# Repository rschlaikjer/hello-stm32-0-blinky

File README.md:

# STM32 Programming with opencm3: Part 0

This repository contains the complete companion code and EAGLE design files
to accompany
[this blog post](https://rhye.org/post/stm32-with-opencm3-0-compiling-and-uploading/),
which details the basics of compiling and flashing code to a `STM32F0`-series MCU.

In this repo:
- `main.cpp`: The main application code. Contains a simple example using GPIOs
and the SysTick timer.
- `stm32f0.ld`: Linker script for the `STM32F070CB` MCU
- `Makefile`: Collection of rules to build and upload code to the MCU
- `.gdbinit`: GDB resource file that automates conencting to an attached Black Magic Probe
- `libopencm3`: Git submodule referencing our version of opencm3.

## Pictures

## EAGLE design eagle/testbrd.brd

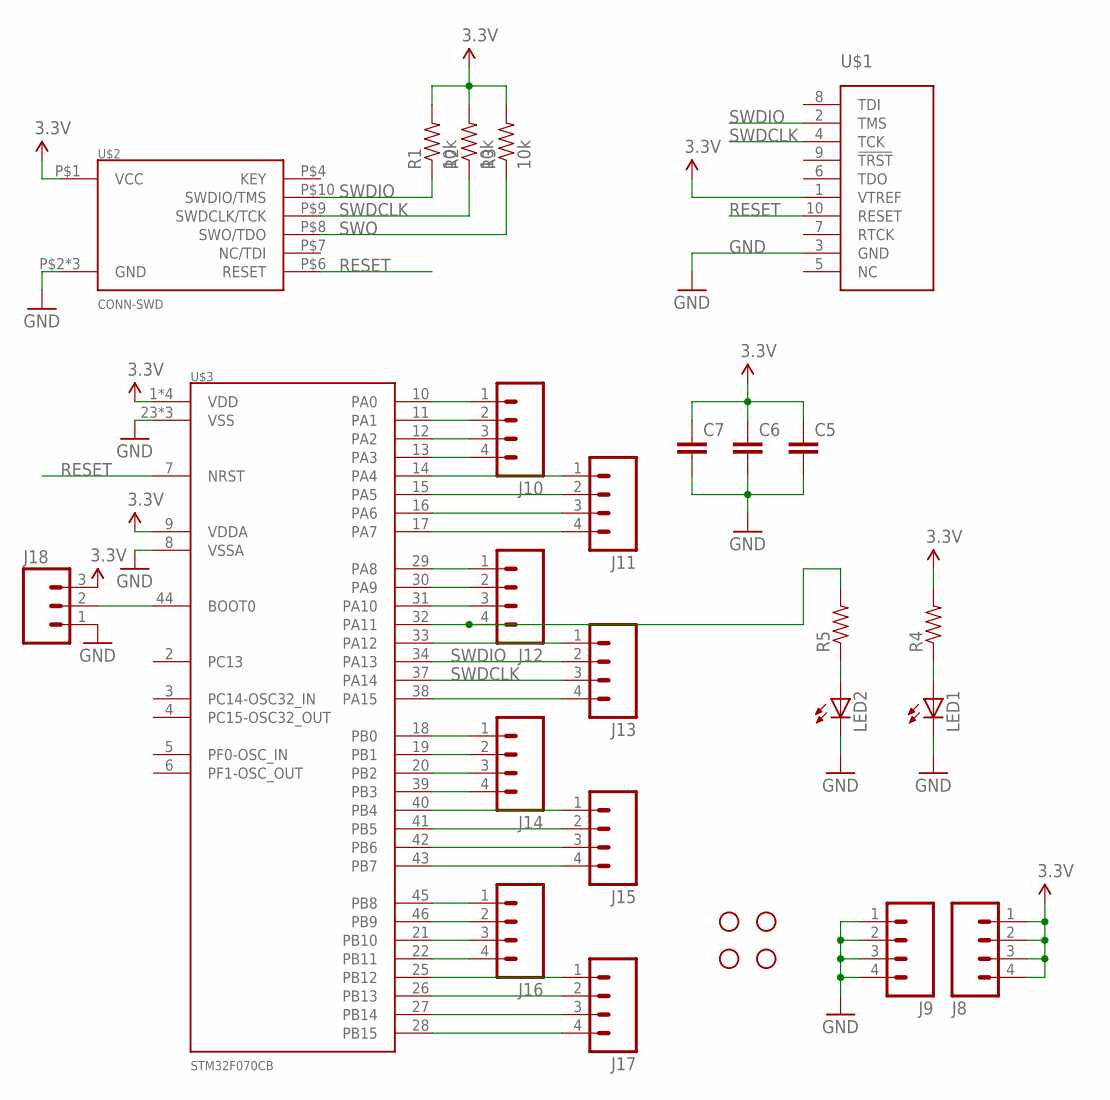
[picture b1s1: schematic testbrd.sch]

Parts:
C5, C6, C7: CAP0805; 0805
H1, H2, H3, H4: STAND-OFF
J8, J9, J10, J11, J12, J13, J14, J15, J16, J17: M04PTH; 1X04
J18: M03PTH; 1X03
LED1, LED2: LEDCHIPLED_0805; CHIPLED_0805
R1, R2, R3: 10k; 0805
R4, R5: RESISTOR0805-RES; 0805
U$1: TC2050-MCP-NL; TC2050
U$2: CONN-SWD; CONN2X5
U$3: STM32F070CB; LQFP-48

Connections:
3.3V: C5.1, C6.1, C7.1, J8.1, J8.2, J8.3, J8.4, J18.3, R1.2, R2.2, R3.2, R4.2, U$1.1 (VTREF), U$2.P$1 (VCC), U$3.1 (VDD), U$3.9 (VDDA), U$3.24 (VDD), U$3.36 (VDD), U$3.48 (VDD)
GND: C5.2, C6.2, C7.2, J9.1, J9.2, J9.3, J9.4, J18.1, LED1.C, LED2.C, U$1.3 (GND), U$2.P$2 (GND), U$2.P$3 (GND), U$2.P$5 (GND), U$3.8 (VSSA), U$3.23 (VSS), U$3.35 (VSS), U$3.47 (VSS)
unnamed: LED1.A, R4.1
unnamed: LED2.A, R5.1
unnamed: J18.2, U$3.44 (BOOT0)
unnamed: J10.1, U$3.10 (PA0)
unnamed: J10.2, U$3.11 (PA1)
unnamed: J10.3, U$3.12 (PA2)
unnamed: J10.4, U$3.13 (PA3)
unnamed: J11.1, U$3.14 (PA4)
unnamed: J11.2, U$3.15 (PA5)
unnamed: J11.3, U$3.16 (PA6)
unnamed: J11.4, U$3.17 (PA7)
unnamed: J12.1, U$3.29 (PA8)
unnamed: J12.2, U$3.30 (PA9)
unnamed: J12.3, U$3.31 (PA10)
unnamed: J12.4, R5.2, U$3.32 (PA11)
unnamed: J13.1, U$3.33 (PA12)
unnamed: J13.4, U$3.38 (PA15)
unnamed: J14.1, U$3.18 (PB0)
unnamed: J14.2, U$3.19 (PB1)
unnamed: J14.3, U$3.20 (PB2)
unnamed: J14.4, U$3.39 (PB3)
unnamed: J15.1, U$3.40 (PB4)
unnamed: J15.2, U$3.41 (PB5)
unnamed: J15.3, U$3.42 (PB6)
unnamed: J15.4, U$3.43 (PB7)
unnamed: J16.1, U$3.45 (PB8)
unnamed: J16.2, U$3.46 (PB9)
unnamed: J16.3, U$3.21 (PB10)
unnamed: J16.4, U$3.22 (PB11)
unnamed: J17.1, U$3.25 (PB12)
unnamed: J17.2, U$3.26 (PB13)
unnamed: J17.3, U$3.27 (PB14)
unnamed: J17.4, U$3.28 (PB15)
RESET: U$1.10 (RESET), U$2.P$6 (RESET), U$3.7 (NRST)
SWDCLK: J13.3, R2.1, U$1.4 (TCK), U$2.P$9 (SWDCLK/TCK), U$3.37 (PA14)
SWDIO: J13.2, R1.1, U$1.2 (TMS), U$2.P$10 (SWDIO/TMS), U$3.34 (PA13)
SWO: R3.1, U$2.P$8 (SWO/TDO)

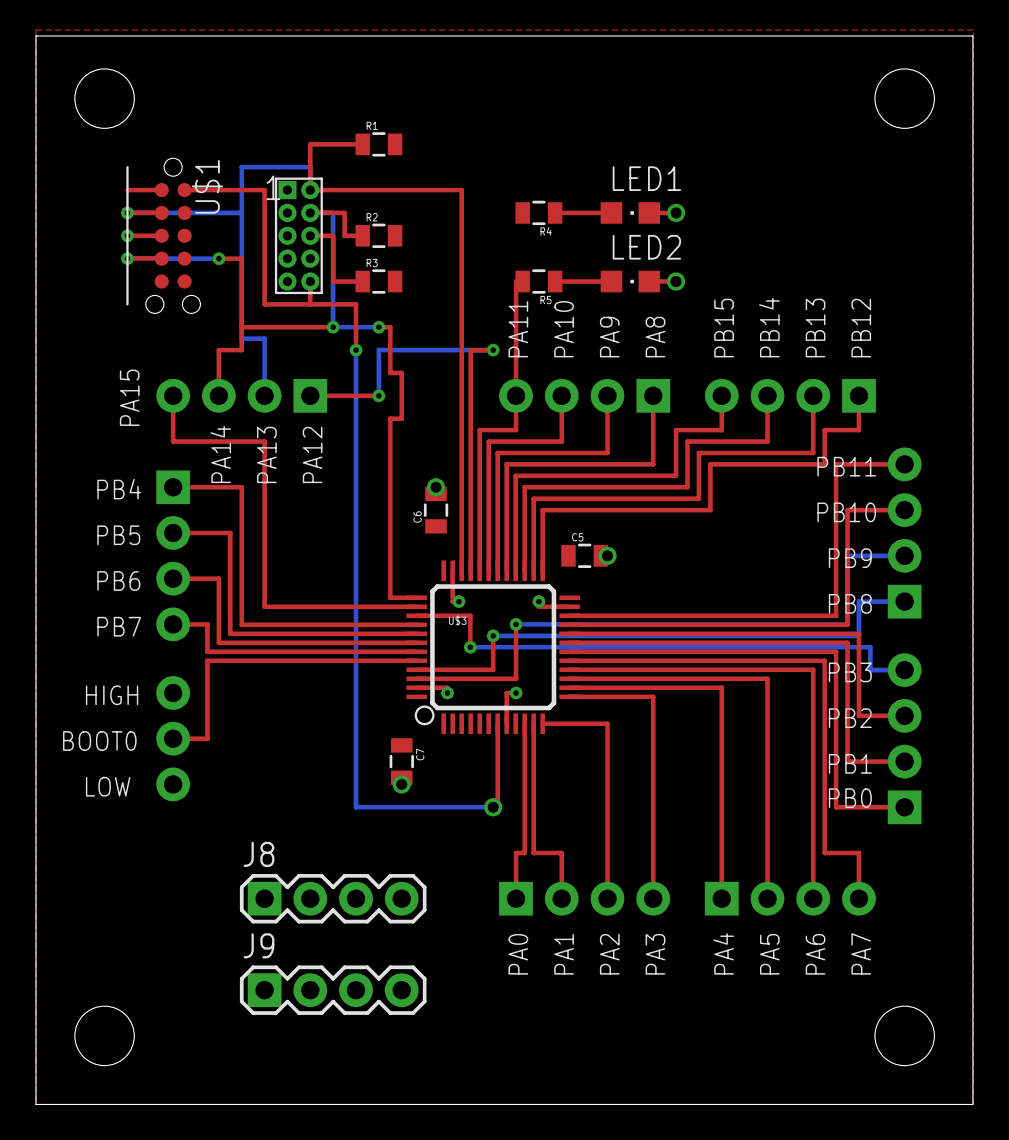
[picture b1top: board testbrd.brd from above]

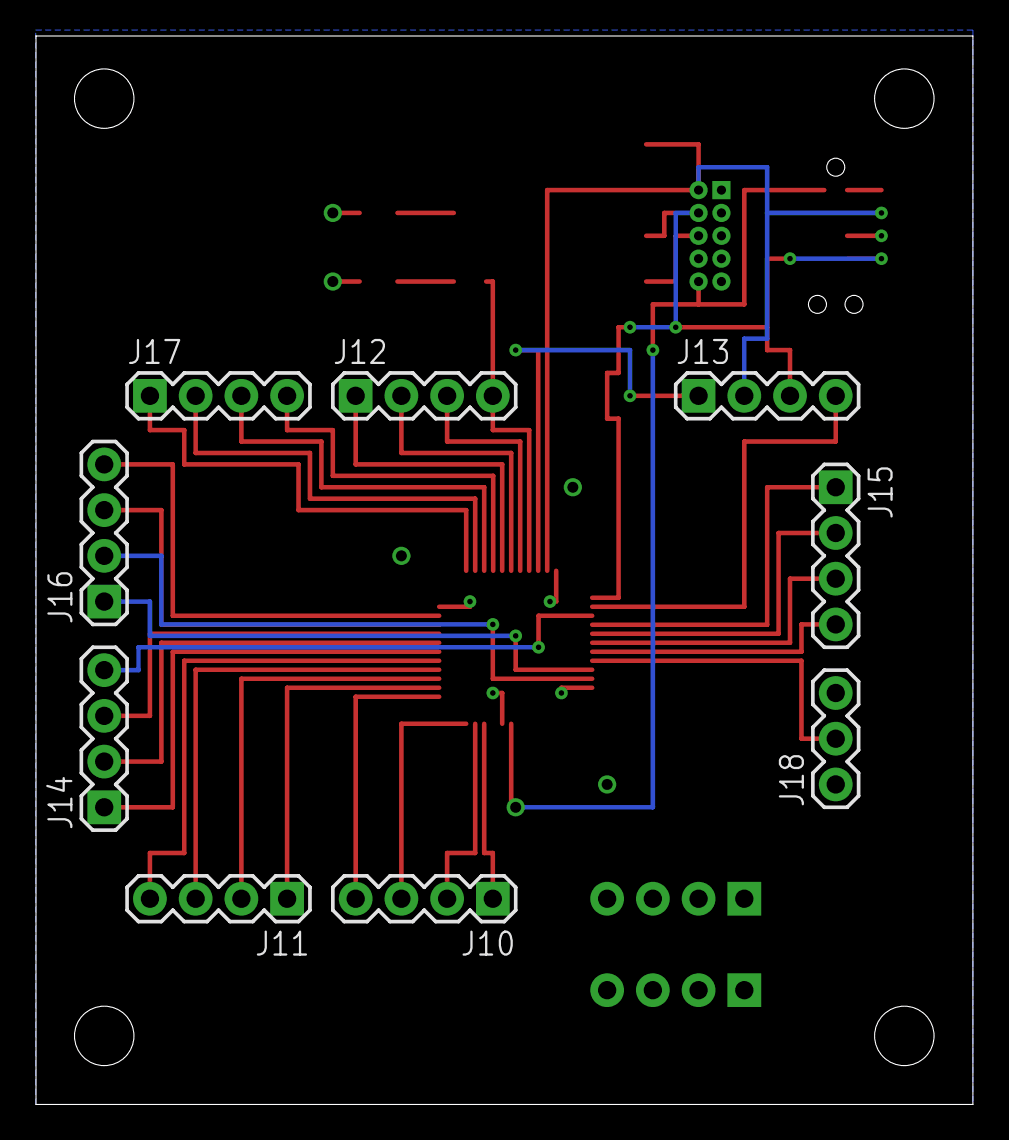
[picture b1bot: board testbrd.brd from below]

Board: 2 copper layers, 52.0 x 59.4 mm, 28 parts (9 on the bottom side), 39 nets.

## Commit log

2018-09-12 Import opencm3
2018-09-12 Demo code
2018-09-12 Linker, Makefile and flash script
2018-09-12 Gitignore and gdbinit
2018-09-12 Add breakout board sources
2018-09-12 Readme for GH

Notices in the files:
parts and their libraries:
SparkFun-Resistors: Licensing: Creative Commons ShareAlike 4.0 International - https://creativecommons.org/licenses/by-sa/4.0
Connector: ©2009 ROFA.cz
